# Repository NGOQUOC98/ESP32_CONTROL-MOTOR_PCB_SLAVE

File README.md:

# PCB_SLAVE
# Kicad_Valve-hardware
# Hardware 

## Schematic

## PCB Layout
### Top side

### Back side

## 3D
### Top side
[]
### Back side
[]
## GERBER
- [Gerber_slave](./assets/gerber/slave.rar)

## REMARK

# LICENSE

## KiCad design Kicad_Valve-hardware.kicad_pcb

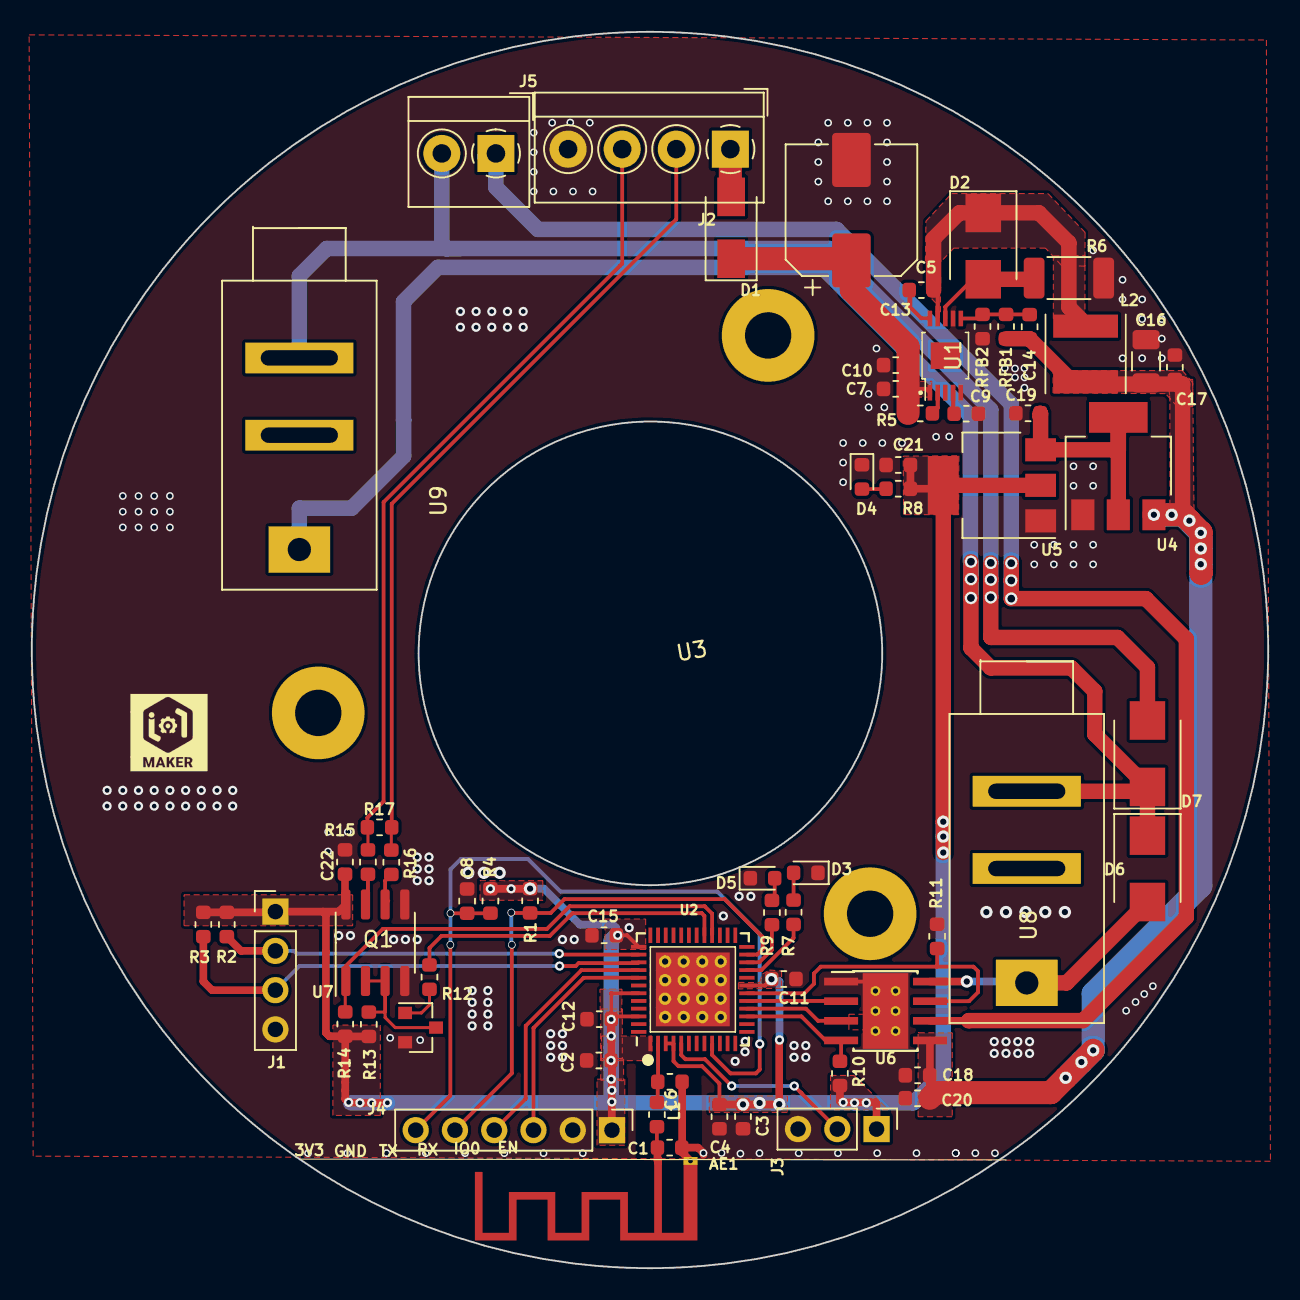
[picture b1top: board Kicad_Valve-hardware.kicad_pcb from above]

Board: 2 copper layers, 80.0 x 80.0 mm, 67 parts (0 on the bottom side), 42 nets.

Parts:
AE1: Antenna_Shield; Texas_SWRA117D_2.4GHz_Right
C1, C6: TBD; C_0603_1608Metric
C2, C3, C7, C11, C12, C13, C15, C17, C18: 100nF; C_0603_1608Metric
C4: 10uF/10V; C_0603_1608Metric
C5: 100uF/50V; CP_Elec_8x10
C8: 0.1uF; C_0603_1608Metric
C9: 10nF; C_0603_1608Metric
C10: 1uF; C_0603_1608Metric
C14: 1nF; C_0603_1608Metric
C16: 10uF; C_1206_3216Metric
C19, C21, C22: 10uF; C_0603_1608Metric
C20: 10uF/35V; C_0603_1608Metric
D1: 1N4007; D_SMA
D2, D6, D7: SS24; D_SMB
D3: GREEN; LED_0603_1608Metric
D4, D5: RED; LED_0603_1608Metric
J1: LIGHT; PinHeader_1x04_P2.54mm_Vertical
J2: Terminal 3.5mm; TerminalBlock_4Ucon_1x04_P3.50mm_Horizontal
J3: SOIL MOISTURE; PinHeader_1x03_P2.54mm_Vertical
J4: Flash; PinHeader_1x06_P2.54mm_Vertical
J5: MOTOR; TerminalBlock_4Ucon_1x02_P3.50mm_Horizontal
L1: TBD; L_0603_1608Metric
L2: 15uH; L_Taiyo-Yuden_MD-5050
Logo1: Logo_IoTMaker; logo-iotmaker-v1
Q1: Q_NMOS_GSD; SOT-23
R1, R2, R3, R4, R10, R14: 10K; R_0603_1608Metric
R5: 267K; R_0603_1608Metric
R6: 80 mOhm; R_2010_5025Metric
R7, R8, R9, R13: 1K; R_0603_1608Metric
R11: Rsense; R_0603_1608Metric
R12: 10; R_0603_1608Metric
R15, R16: 680R; R_0603_1608Metric
R17: 120R; R_0603_1608Metric
RFB1: 37.4K; R_0603_1608Metric
RFB2: 9.76K; R_0603_1608Metric
U1: LM25011MY; HVSSOP-10-1EP_3X3MM_P0.5MM_EP1.73x1.73
U2: ESP32-PICO-D4; QFN-48-1EP_7x7mm_P0.5mm
U3: Hole_THT
U4: AMS1117-5.0; SOT-223-3_TabPin2
U5: AMS1117-3.3; SOT-223-3_TabPin2
U6: DRV8872DDA; Texas_HTSOP-8-1EP_3.9x4.9mm_P1.27mm_EP2.95x4.9mm_Mask2.4x3.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
U7: SP3485; SOIC-8_3.9x4.9mm_P1.27mm
U8, U9: KW8-XILIE

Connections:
+3V3: C2.2, C3.2, C4.1, C11.2, C12.2, C15.1, C21.1, C22.1, J1.1, J3.1, J4.1, R1.1, R2.1, R3.1, R4.1, R8.1, R10.1, R13.2, R14.1, U2.1, U2.3, U2.4, U2.19, U2.37, U2.43, U2.46, U5.2, U7.8
+5V: C19.1, U4.2, U5.3
+12V: C14.1, C16.1, C17.1, C18.2, C20.1, L2.2, RFB1.1, U4.3, U6.5
ADC_IN: J3.2, U2.5
DRV_IN1: U2.16, U6.3
DRV_IN2: U2.17, U6.2
DRV_ISEN: R11.2, U2.18, U6.7
DRV_nFAULT: R10.2, U2.15, U6.4
FLASH_EN: C8.1, J4.6, R4.2, U2.9
FLASH_IO0: J4.5, R1.2, U2.23
FLASH_U0RX: J4.4, U2.40
FLASH_U0TX: J4.3, U2.41
GND: AE1.2, C1.2, C2.1, C3.1, C4.2, C5.2, C6.2, C7.2, C8.2, C9.2, C10.1, C11.1, C12.1, C15.2, C16.2, C17.2, C18.1, C19.2, C20.2, C21.2, C22.2, D3.1, D4.1, D5.1, J1.4, J2.4, J3.3, J4.2, Q1.2, R6.2, R11.1, RFB2.2, U1.5, U1.7, U2.49, U4.1, U5.1, U6.1, U6.9, U7.4, U7.5
LED1: R7.1, U2.21
LED2: R9.2, U2.22
unnamed: AE1.1, C1.1, L1.1
unnamed: C6.1, L1.2, U2.2
unnamed: C9.1, U1.4
unnamed: C5.1, C7.1, C10.2, D1.1, R5.2, U1.1
unnamed: C13.1, D2.1, L2.1, U1.9
unnamed: C13.2, U1.10
unnamed: C14.2, RFB1.2, RFB2.1, U1.6
unnamed: D1.2, J2.1
unnamed: D2.2, R6.1, U1.8
unnamed: D3.2, R7.2
unnamed: D4.2, R8.2
unnamed: D5.2, R9.1
unnamed: D6.1, D7.1, U8.3, U9.1
unnamed: D6.2, U6.8, U8.1
unnamed: D7.2, J5.2, U9.3
unnamed: J5.1, U6.6
unnamed: Q1.1, R12.2
unnamed: Q1.3, R13.1, U7.2, U7.3
unnamed: R5.1, U1.2
unnamed: R15.2, U7.7
unnamed: R16.2, U7.6
RS485_A: J2.3, R15.1, R17.2
RS485_B: J2.2, R16.1, R17.1
RS485_RX: R14.2, U2.28, U7.1
RS485_TX: R12.1, U2.29
SS_SCL: J1.3, R3.2, U2.39
SS_SDA: J1.2, R2.2, U2.38

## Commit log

2020-10-14 add file
